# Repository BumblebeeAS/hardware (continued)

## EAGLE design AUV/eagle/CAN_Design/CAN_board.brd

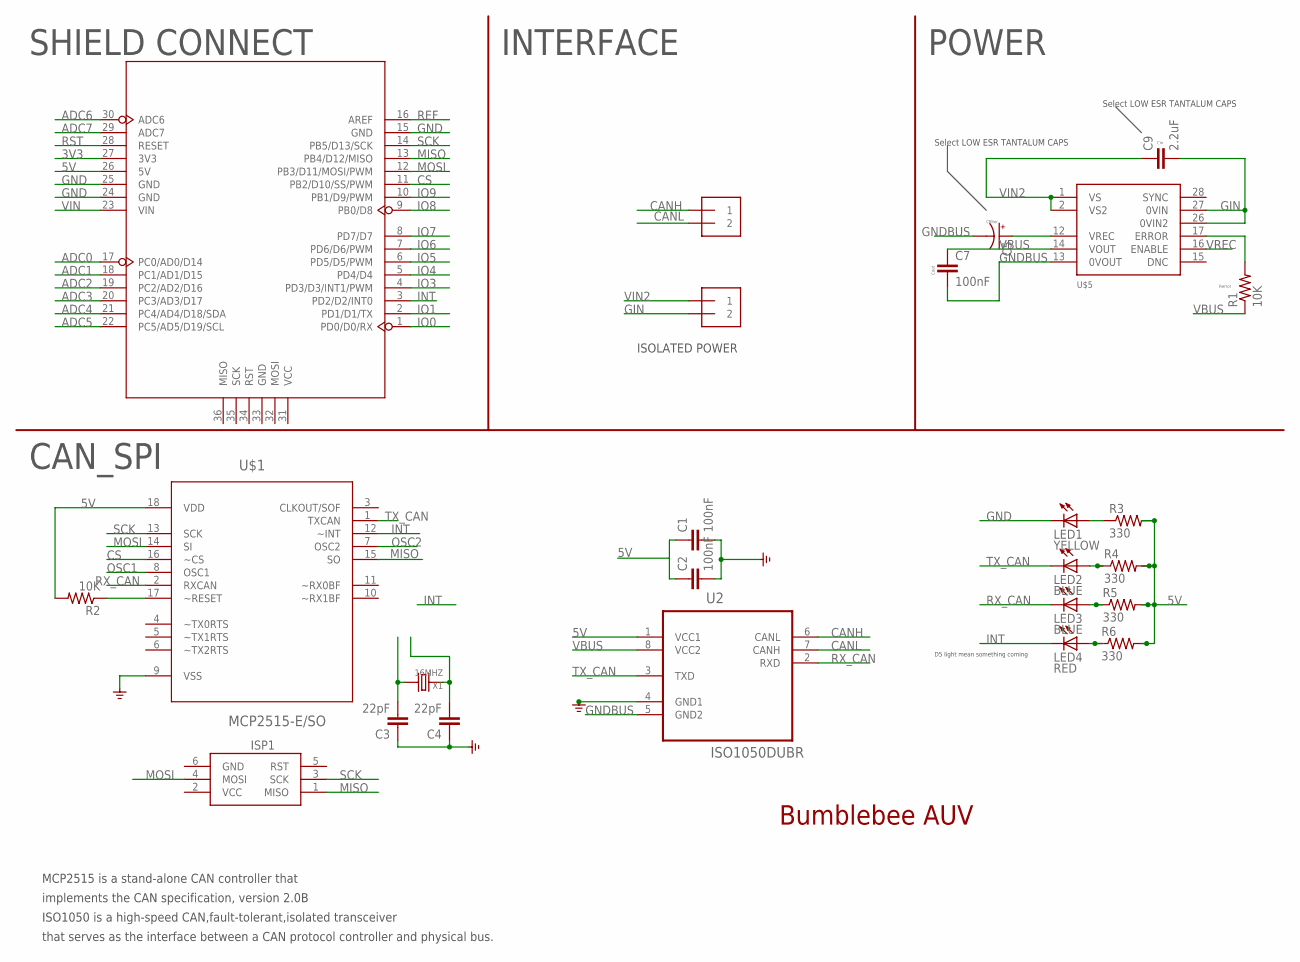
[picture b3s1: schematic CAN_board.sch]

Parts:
C1, C2, C7: 100nF; 0805
C3, C4: 22pF; 0805; MPN MC0603N220K500CT
C5: CAP_POL6032; EIA6032
C9: 2.2uF; 0603-CAP
ISP1: AVRISP-6; AVRISP
J0, J1: 1X2-3.5MM
LED1: YELLOW; CHIPLED_0805
LED2, LED3: BLUE; CHIPLED_0805
LED4: RED; CHIPLED_0805
R1, R2: 10K; 0805
R3, R4, R5, R6: 330; 0805
U2: ISO1050DUBR; SOIC254P1040X485-8N
U3: ARDUINO
U$1: MCP2515-E/SO; SOIC127P1030X265-18N
U$5: DCR01SO; DCR01-SOIC28
X1: 16MHZ; HC49US; MPN HC49US16.000MABJ-UB

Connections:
3V3: U3.27 (3V3)
5V: C1.1, C2.1, R2.2, R3.2, R4.2, R5.2, R6.2, U3.26 (5V), U$1.18 (VDD)
ADC0: U3.17 (PC0/AD0/D14)
ADC1: U3.18 (PC1/AD1/D15)
ADC2: U3.19 (PC2/AD2/D16)
ADC3: U3.20 (PC3/AD3/D17)
ADC4: U3.21 (PC4/AD4/D18/SDA)
ADC5: U3.22 (PC5/AD5/D19/SCL)
ADC6: U3.30 (ADC6)
ADC7: U3.29 (ADC7)
CANH: J0.1
CANL: J0.2
CS: U3.11 (PB2/D10/SS/PWM)
ERROR: R1.2, U$5.17 (ERROR)
GIN: C9.2, J1.2, U$5.26 (0VIN2), U$5.27 (0VIN)
GND: C1.2, C2.2, C3.1, C4.1, ISP1.6 (GND), LED1.C, U3.15 (GND), U3.24 (GND), U3.25 (GND), U$1.9 (VSS)
GNDBUS: C5.P$2 (-), C7.2, U$5.13 (0VOUT)
INT: LED4.C, U3.3 (PD2/D2/INT0), U$1.12 (~INT)
IO0: U3.1 (PD0/D0/RX)
IO1: U3.2 (PD1/D1/TX)
IO3: U3.4 (PD3/D3/INT1/PWM)
IO4: U3.5 (PD4/D4)
IO5: U3.6 (PD5/D5/PWM)
IO6: U3.7 (PD6/D6/PWM)
IO7: U3.8 (PD7/D7)
IO8: U3.9 (PB0/D8)
IO9: U3.10 (PB1/D9/PWM)
MISO: ISP1.1 (MISO), U3.13 (PB4/D12/MISO)
MOSI: ISP1.4 (MOSI), U3.12 (PB3/D11/MOSI/PWM)
unnamed: LED1.A, R3.1
unnamed: LED2.A, R4.1
unnamed: R2.1, U$1.17 (~RESET)
unnamed: LED3.A, R5.1
unnamed: LED4.A, R6.1
OSC1: C3.2, U$1.8 (OSC1), X1.2
OSC2: C4.2, U$1.7 (OSC2), X1.1
REF: U3.16 (AREF)
RST: U3.28 (RESET)
RX_CAN: LED3.C
SCK: ISP1.3 (SCK), U3.14 (PB5/D13/SCK)
TX_CAN: LED2.C
VBUS: C7.1, R1.1, U$5.14 (VOUT)
VCC: ISP1.2 (VCC)
VCC1: U2.1 (VCC1)
VCC2: U2.8 (VCC2)
VIN: U3.23 (VIN)
VIN2: C9.1, J1.1, U$5.1 (VS), U$5.2 (VS2)
VREC: C5.P$1 (+), U$5.12 (VREC), U$5.16 (ENABLE)

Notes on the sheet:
CAN_SPI
SHIELD CONNECT
INTERFACE
POWER
D5 light mean something coming
MCP2515 is a stand-alone CAN controller that
ISO1050 is a high-speed CAN,fault-tolerant,isolated transceiver
that serves as the interface between a CAN protocol controller and physical bus.
implements the CAN specification, version 2.0B
Bumblebee AUV
ISOLATED POWER
Cfilter
Cout
Cin
Rerror
Select LOW ESR TANTALUM CAPS

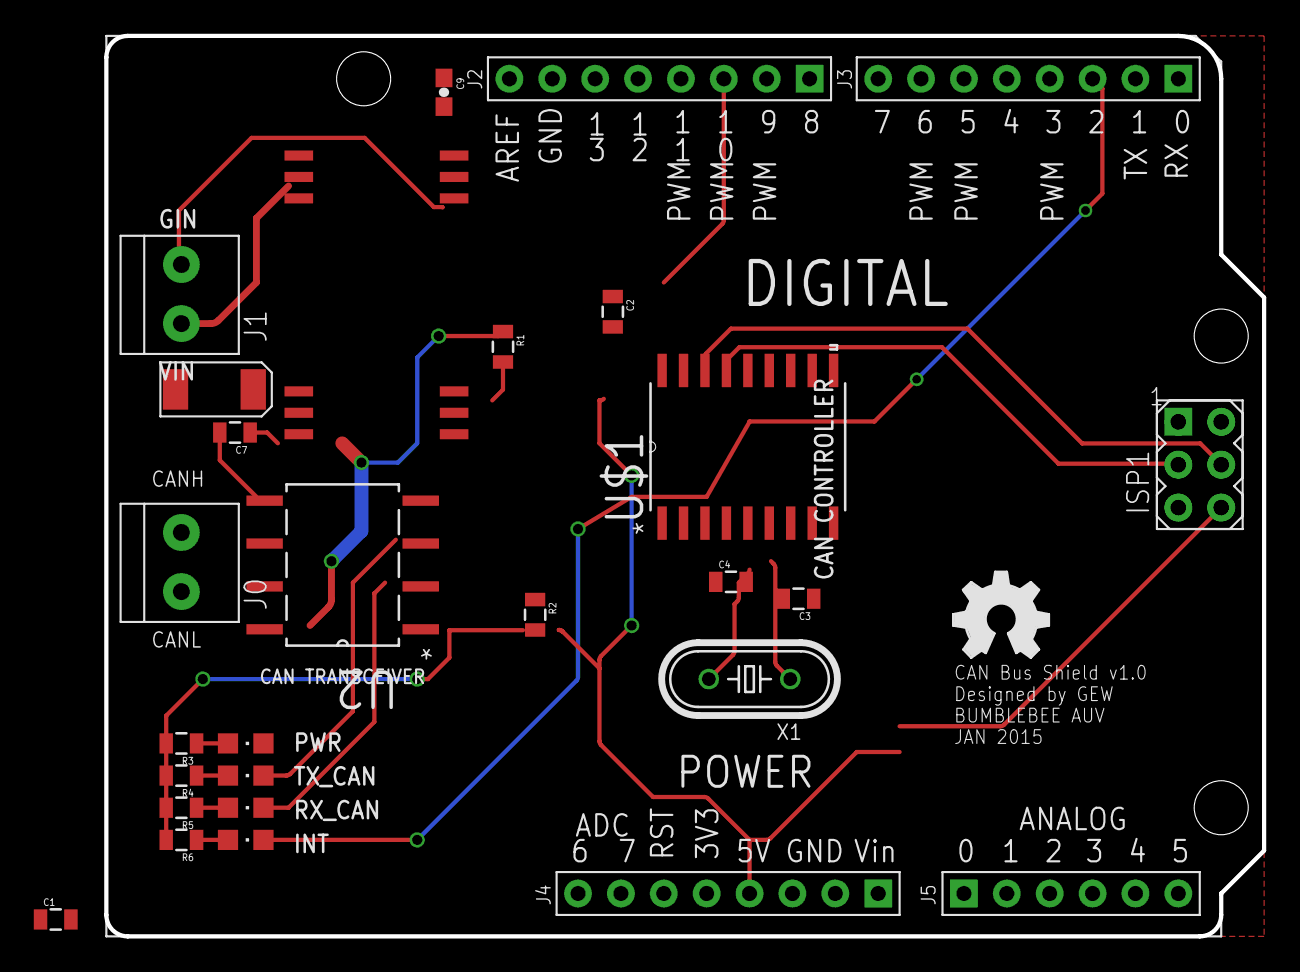
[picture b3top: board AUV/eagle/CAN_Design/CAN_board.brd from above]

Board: 4 copper layers, 68.6 x 53.3 mm, 26 parts (0 on the bottom side), 19 nets.

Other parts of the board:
U$2: OSHW_FILLX200_NOTEXT

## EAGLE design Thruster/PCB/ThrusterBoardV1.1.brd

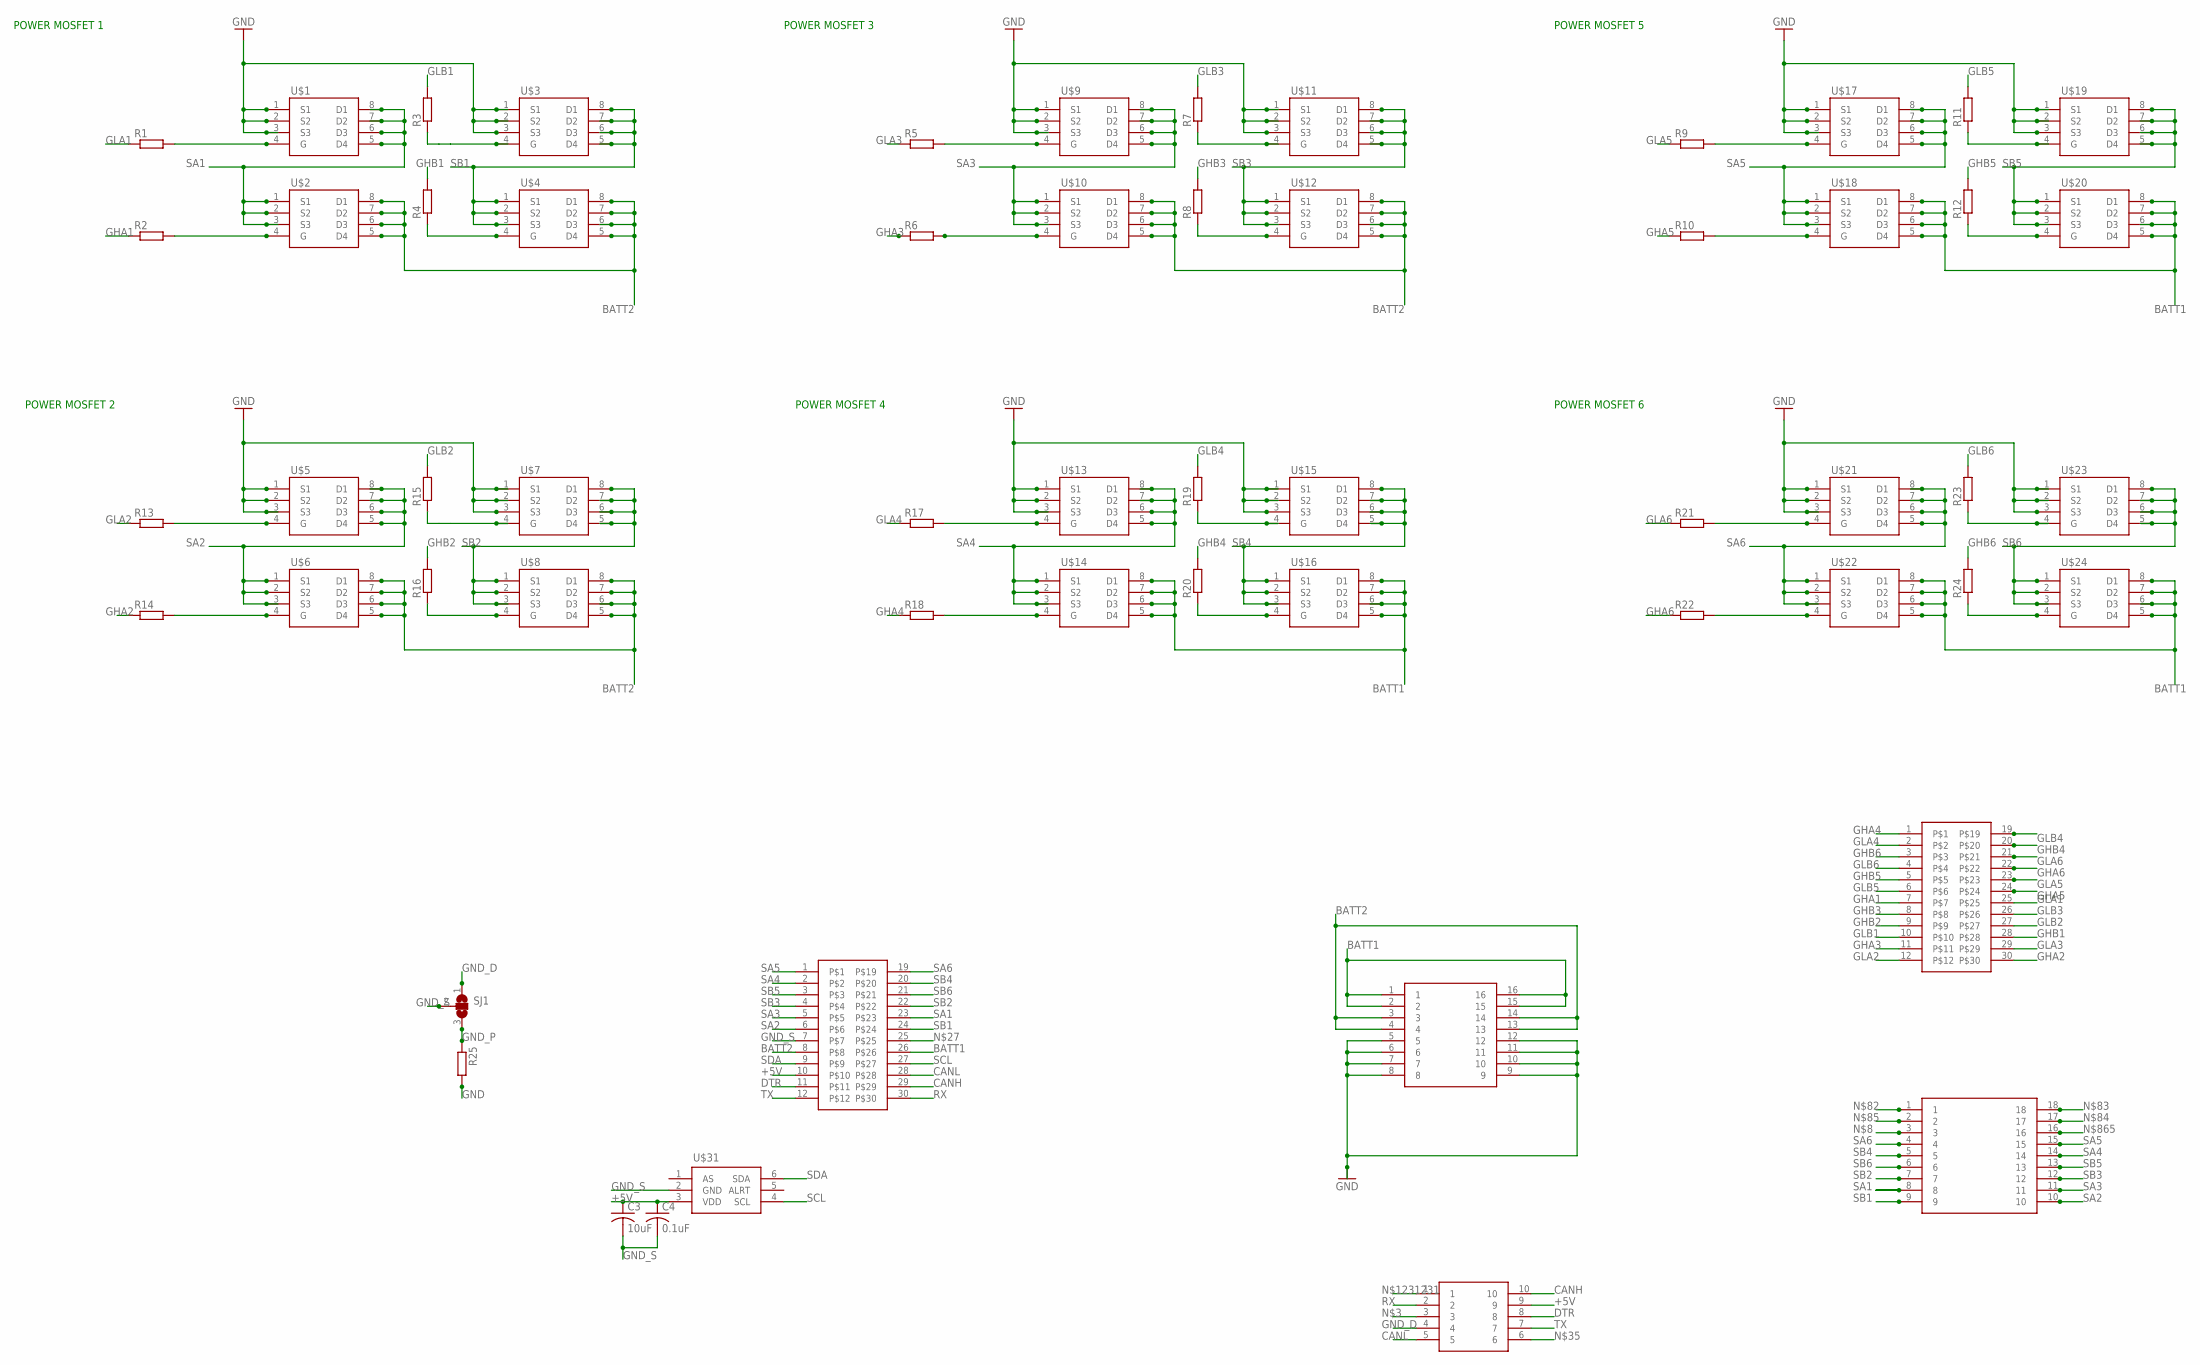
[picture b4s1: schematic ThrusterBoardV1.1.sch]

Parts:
C3: 10uF; C0805
C4: 0.1uF; C0805
R1, R2, R3, R4, R5, R6, R7, R8, R9, R10, R11, R12, R13, R14, R15, R16, R17, R18, R19, R20, R21, R22, R23, R24, R25: R; R0805
SJ1: SJ2W; SJ_2
U$1, U$2, U$3, U$4, U$5, U$6, U$7, U$8, U$9, U$10, U$11, U$12, U$13, U$14, U$15, U$16, U$17, U$18, U$19, U$20, U$21, U$22, U$23, U$24: IRF7842PBF; SO-8
U$25: 15-24-6163
U$26: 50-36-1836
U$27: 15-24-6103
U$28, U$29: 15-45-3136
U$31: AD7414; SOT23-6

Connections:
+5V: C3.1, C4.1, U$27.9, U$29.10, U$31.3 (VDD)
ASDASD: R2.2, U$2.4 (G)
BATT1: U$14.5 (D4), U$14.6 (D3), U$14.7 (D2), U$14.8 (D1), U$16.5 (D4), U$16.6 (D3), U$16.7 (D2), U$16.8 (D1), U$18.5 (D4), U$18.6 (D3), U$18.7 (D2), U$18.8 (D1), U$20.5 (D4), U$20.6 (D3), U$20.7 (D2), U$20.8 (D1), U$22.5 (D4), U$22.6 (D3), U$22.7 (D2), U$22.8 (D1), U$24.5 (D4), U$24.6 (D3), U$24.7 (D2), U$24.8 (D1), U$25.1, U$25.2, U$25.15, U$25.16, U$29.26
BATT2: U$2.5 (D4), U$2.6 (D3), U$2.7 (D2), U$2.8 (D1), U$4.5 (D4), U$4.6 (D3), U$4.7 (D2), U$4.8 (D1), U$6.5 (D4), U$6.6 (D3), U$6.7 (D2), U$6.8 (D1), U$8.5 (D4), U$8.6 (D3), U$8.7 (D2), U$8.8 (D1), U$10.5 (D4), U$10.6 (D3), U$10.7 (D2), U$10.8 (D1), U$12.5 (D4), U$12.6 (D3), U$12.7 (D2), U$12.8 (D1), U$25.3, U$25.4, U$25.13, U$25.14, U$29.8
CANH: U$27.10, U$29.29
CANL: U$27.5, U$29.28
DTR: U$27.8, U$29.11
GHA1: R2.1, U$28.7
GHA2: R14.1, U$28.30
GHA3: R6.1, U$28.11
GHA4: R18.1, U$28.1
GHA5: R10.1, U$28.24
GHA6: R22.1, U$28.22
GHB1: R4.2, U$28.28
GHB2: R16.2, U$28.9
GHB3: R8.2, U$28.8
GHB4: R20.2, U$28.20
GHB5: R12.2, U$28.5
GHB6: R24.2, U$28.3
GLA1: R1.1, U$28.25
GLA2: R13.1, U$28.12
GLA3: R5.1, U$28.29
GLA4: R17.1, U$28.2
GLA5: R9.1, U$28.23
GLA6: R21.1, U$28.21
GLB1: R3.2, U$28.10
GLB2: R15.2, U$28.27
GLB3: R7.2, U$28.26
GLB4: R19.2, U$28.19
GLB5: R11.2, U$28.6
GLB6: R23.2, U$28.4
GND: R25.2, U$1.1 (S1), U$1.2 (S2), U$1.3 (S3), U$3.1 (S1), U$3.2 (S2), U$3.3 (S3), U$5.1 (S1), U$5.2 (S2), U$5.3 (S3), U$7.1 (S1), U$7.2 (S2), U$7.3 (S3), U$9.1 (S1), U$9.2 (S2), U$9.3 (S3), U$11.1 (S1), U$11.2 (S2), U$11.3 (S3), U$13.1 (S1), U$13.2 (S2), U$13.3 (S3), U$15.1 (S1), U$15.2 (S2), U$15.3 (S3), U$17.1 (S1), U$17.2 (S2), U$17.3 (S3), U$19.1 (S1), U$19.2 (S2), U$19.3 (S3), U$21.1 (S1), U$21.2 (S2), U$21.3 (S3), U$23.1 (S1), U$23.2 (S2), U$23.3 (S3), U$25.5, U$25.6, U$25.7, U$25.8, U$25.9, U$25.10, U$25.11, U$25.12
GND_D: SJ1.1, U$27.4
GND_P: R25.1, SJ1.3
GND_S: C3.2, C4.2, SJ1.2, U$29.7, U$31.2 (GND)
unnamed: R3.1, U$3.4 (G)
unnamed: R4.1, U$4.4 (G)
unnamed: R5.2, U$9.4 (G)
unnamed: R6.2, U$10.4 (G)
unnamed: R7.1, U$11.4 (G)
unnamed: R8.1, U$12.4 (G)
unnamed: R9.2, U$17.4 (G)
unnamed: R10.2, U$18.4 (G)
unnamed: R11.1, U$19.4 (G)
unnamed: R12.1, U$20.4 (G)
unnamed: R13.2, U$5.4 (G)
unnamed: R14.2, U$6.4 (G)
unnamed: R16.1, U$8.4 (G)
unnamed: R15.1, U$7.4 (G)
unnamed: R17.2, U$13.4 (G)
unnamed: R18.2, U$14.4 (G)
unnamed: R20.1, U$16.4 (G)
unnamed: R19.1, U$15.4 (G)
unnamed: R21.2, U$21.4 (G)
unnamed: R22.2, U$22.4 (G)
unnamed: R23.1, U$23.4 (G)
unnamed: R24.1, U$24.4 (G)
unnamed: R1.2, U$1.4 (G)
RX: U$27.2, U$29.30
SA1: U$1.5 (D4), U$1.6 (D3), U$1.7 (D2), U$1.8 (D1), U$2.1 (S1), U$2.2 (S2), U$2.3 (S3), U$26.8, U$29.23
SA2: U$5.5 (D4), U$5.6 (D3), U$5.7 (D2), U$5.8 (D1), U$6.1 (S1), U$6.2 (S2), U$6.3 (S3), U$26.10, U$29.6
SA3: U$9.5 (D4), U$9.6 (D3), U$9.7 (D2), U$9.8 (D1), U$10.1 (S1), U$10.2 (S2), U$10.3 (S3), U$26.11, U$29.5
SA4: U$13.5 (D4), U$13.6 (D3), U$13.7 (D2), U$13.8 (D1), U$14.1 (S1), U$14.2 (S2), U$14.3 (S3), U$26.14, U$29.2
SA5: U$17.5 (D4), U$17.6 (D3), U$17.7 (D2), U$17.8 (D1), U$18.1 (S1), U$18.2 (S2), U$18.3 (S3), U$26.15, U$29.1
SA6: U$21.5 (D4), U$21.6 (D3), U$21.7 (D2), U$21.8 (D1), U$22.1 (S1), U$22.2 (S2), U$22.3 (S3), U$26.4, U$29.19
SB1: U$3.5 (D4), U$3.6 (D3), U$3.7 (D2), U$3.8 (D1), U$4.1 (S1), U$4.2 (S2), U$4.3 (S3), U$26.9, U$29.24
SB2: U$7.5 (D4), U$7.6 (D3), U$7.7 (D2), U$7.8 (D1), U$8.1 (S1), U$8.2 (S2), U$8.3 (S3), U$26.7, U$29.22
SB3: U$11.5 (D4), U$11.6 (D3), U$11.7 (D2), U$11.8 (D1), U$12.1 (S1), U$12.2 (S2), U$12.3 (S3), U$26.12, U$29.4
SB4: U$15.5 (D4), U$15.6 (D3), U$15.7 (D2), U$15.8 (D1), U$16.1 (S1), U$16.2 (S2), U$16.3 (S3), U$26.5, U$29.20
SB5: U$19.5 (D4), U$19.6 (D3), U$19.7 (D2), U$19.8 (D1), U$20.1 (S1), U$20.2 (S2), U$20.3 (S3), U$26.13, U$29.3
SB6: U$23.5 (D4), U$23.6 (D3), U$23.7 (D2), U$23.8 (D1), U$24.1 (S1), U$24.2 (S2), U$24.3 (S3), U$26.6, U$29.21
SCL: U$29.27, U$31.4 (SCL)
SDA: U$29.9, U$31.6 (SDA)
TX: U$27.7, U$29.12

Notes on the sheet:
POWER MOSFET 1
POWER MOSFET 2
POWER MOSFET 3
POWER MOSFET 4
POWER MOSFET 5
POWER MOSFET 6

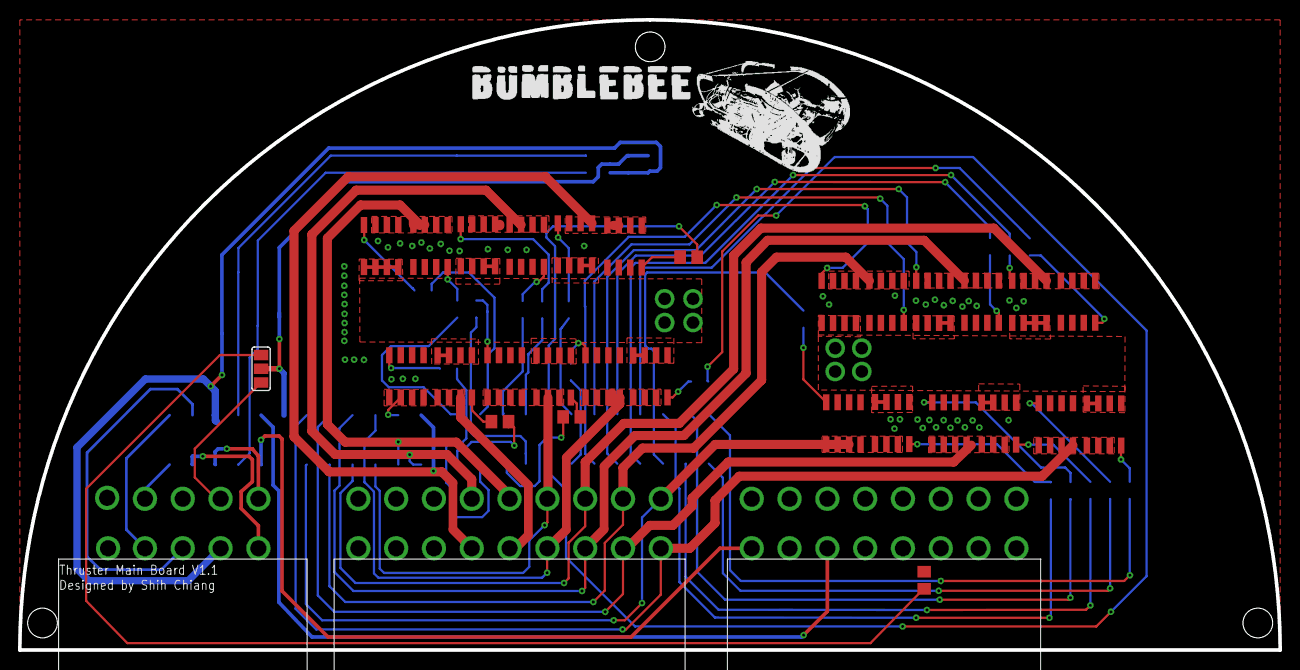
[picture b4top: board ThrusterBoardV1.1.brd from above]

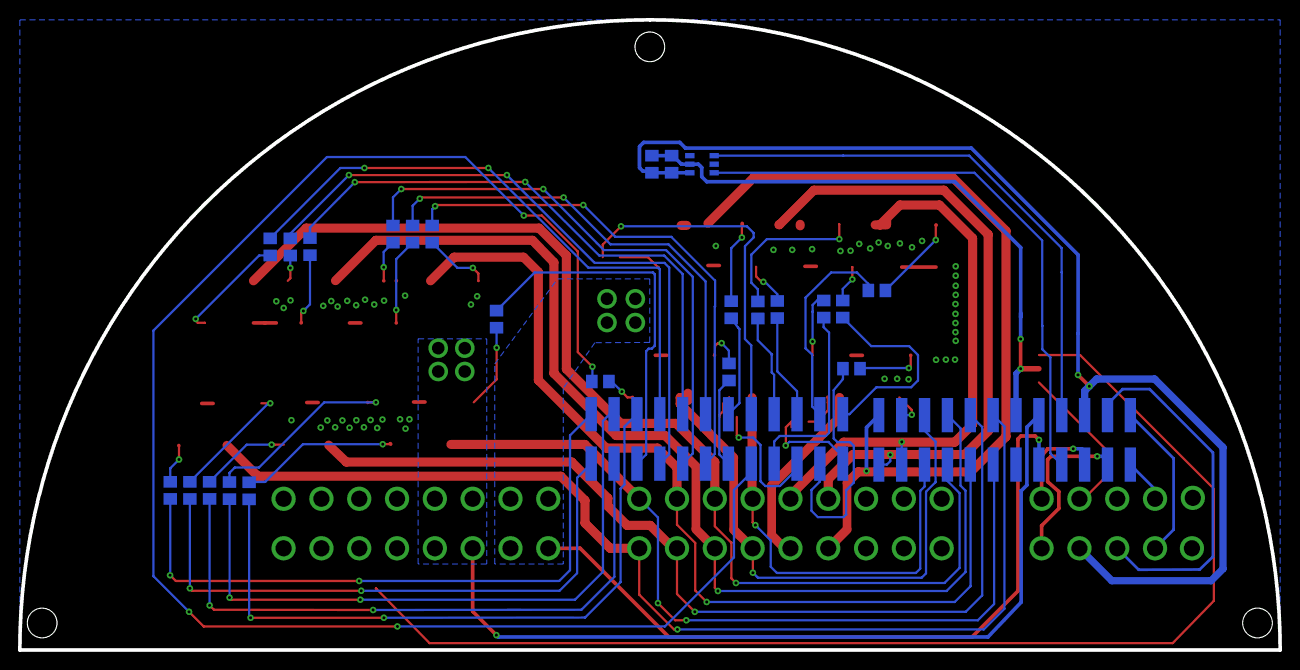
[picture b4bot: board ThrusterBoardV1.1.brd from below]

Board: 2 copper layers, 140.0 x 70.0 mm, 58 parts (26 on the bottom side), 74 nets.

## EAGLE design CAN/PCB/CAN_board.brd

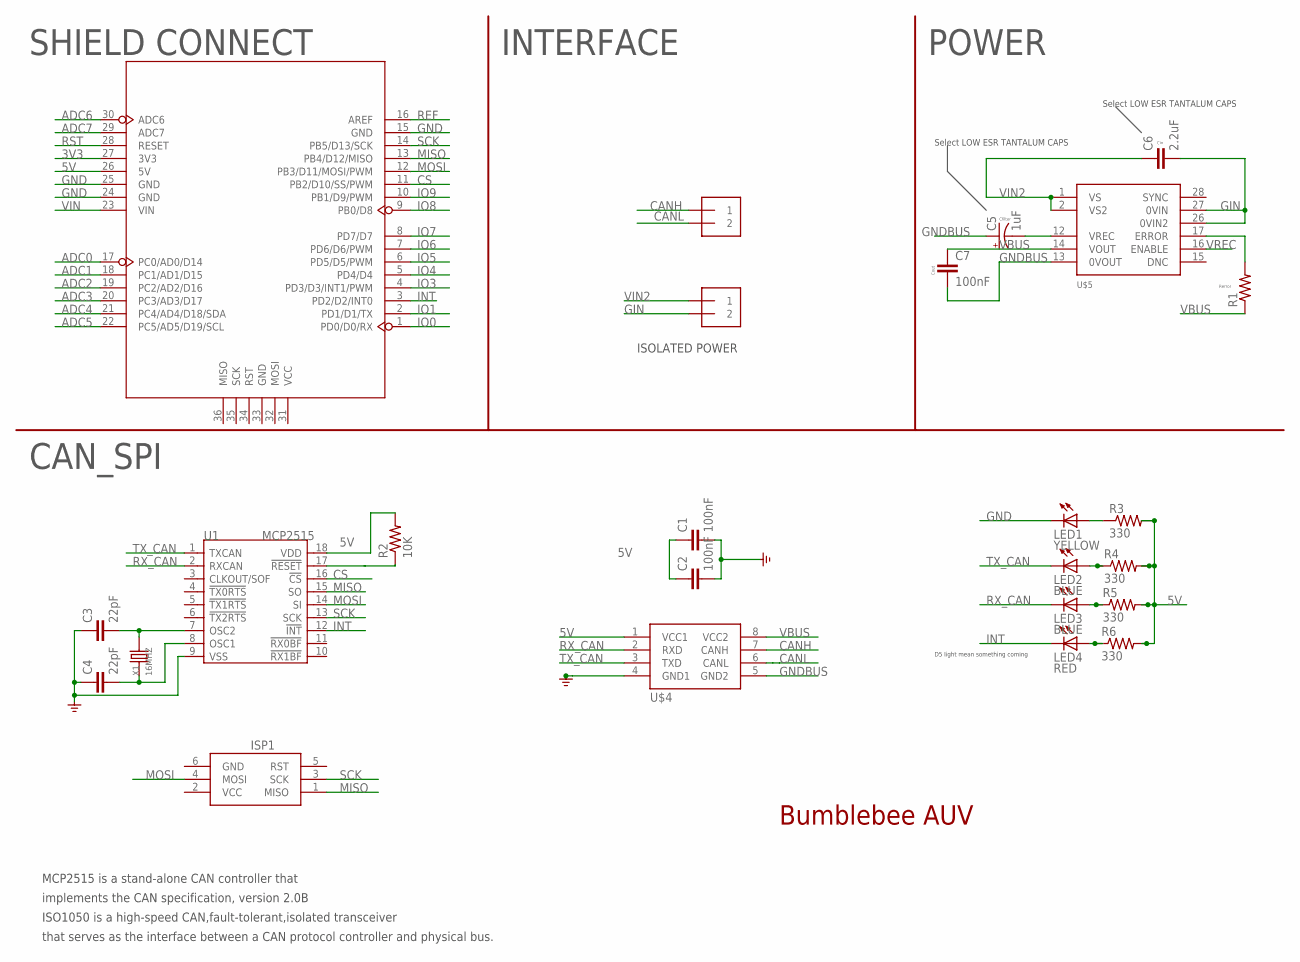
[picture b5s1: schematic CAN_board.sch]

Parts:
C1, C2, C7: 100nF; 0805; MPN MC0805B104K250CT
C3, C4: 22pF; 0805; MPN MC0603N220K500CT
C5: 1uF; EIA6032; MPN TR3C105K050C1600
C6: 2.2uF; 0603-CAP; MPN F381A225MMA
ISP1: AVRISP-6; AVRISP
J0, J1: 1X2-3.5MM
LED1: YELLOW; CHIPLED_0805; MPN KPT-2012SYCK-J3
LED2, LED3: BLUE; CHIPLED_0805; MPN 150080BS75000
LED4: RED; CHIPLED_0805; MPN KPT-2012SRC-J4
R1: RESISTOR0805-RES; 0805
R2: 10K; 0805; MPN CRCW080510K0FKTA
R3, R4, R5, R6: 330; 0805; MPN MCHP05W4F3300T5E
U1: MCP2515; SOIC18; MPN MCP2515-I/SO
U3: ARDUINO
U$4: ISO1050; DUB-8; MPN ISO1050DUBR
U$5: DCR01SO; DCR01-SOIC28; MPN DCR010505U
X1: 16MHZ; HC49US; MPN HC-49/U-S16000000ABJB

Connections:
3V3: U3.27 (3V3)
5V: C1.1, C2.1, R2.2, R3.2, R4.2, R5.2, R6.2, U1.18 (VDD), U3.26 (5V), U$4.1 (VCC1)
ADC0: U3.17 (PC0/AD0/D14)
ADC1: U3.18 (PC1/AD1/D15)
ADC2: U3.19 (PC2/AD2/D16)
ADC3: U3.20 (PC3/AD3/D17)
ADC4: U3.21 (PC4/AD4/D18/SDA)
ADC5: U3.22 (PC5/AD5/D19/SCL)
ADC6: U3.30 (ADC6)
ADC7: U3.29 (ADC7)
CANH: J0.1, U$4.7 (CANH)
CANL: J0.2, U$4.6 (CANL)
CS: U1.16 (!CS), U3.11 (PB2/D10/SS/PWM)
ERROR: R1.2, U$5.17 (ERROR)
GIN: C6.2, J1.2, U$5.26 (0VIN2), U$5.27 (0VIN)
GND: C1.2, C2.2, C3.1, C4.1, ISP1.6 (GND), LED1.C, U1.9 (VSS), U3.15 (GND), U3.24 (GND), U3.25 (GND), U$4.4 (GND1)
GNDBUS: C5.P$1 (+), C7.2, U$4.5 (GND2), U$5.13 (0VOUT)
INT: LED4.C, U1.12 (!INT), U3.3 (PD2/D2/INT0)
IO0: U3.1 (PD0/D0/RX)
IO1: U3.2 (PD1/D1/TX)
IO3: U3.4 (PD3/D3/INT1/PWM)
IO4: U3.5 (PD4/D4)
IO5: U3.6 (PD5/D5/PWM)
IO6: U3.7 (PD6/D6/PWM)
IO7: U3.8 (PD7/D7)
IO8: U3.9 (PB0/D8)
IO9: U3.10 (PB1/D9/PWM)
MISO: ISP1.1 (MISO), U1.15 (SO), U3.13 (PB4/D12/MISO)
MOSI: ISP1.4 (MOSI), U1.14 (SI), U3.12 (PB3/D11/MOSI/PWM)
unnamed: LED1.A, R3.1
unnamed: LED2.A, R4.1
unnamed: LED3.A, R5.1
unnamed: C3.2, U1.7 (OSC2), X1.2
unnamed: C4.2, U1.8 (OSC1), X1.1
unnamed: LED4.A, R6.1
REF: U3.16 (AREF)
RST: U3.28 (RESET)
RST_N: R2.1, U1.17 (!RESET)
RX_CAN: LED3.C, U1.2 (RXCAN), U$4.2 (RXD)
SCK: ISP1.3 (SCK), U1.13 (SCK), U3.14 (PB5/D13/SCK)
TX_CAN: LED2.C, U1.1 (TXCAN), U$4.3 (TXD)
VBUS: C7.1, R1.1, U$4.8 (VCC2), U$5.14 (VOUT)
VCC: ISP1.2 (VCC)
VIN: U3.23 (VIN)
VIN2: C6.1, J1.1, U$5.1 (VS), U$5.2 (VS2)
VREC: C5.P$2 (-), U$5.12 (VREC), U$5.16 (ENABLE)

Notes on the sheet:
CAN_SPI
SHIELD CONNECT
INTERFACE
POWER
D5 light mean something coming
MCP2515 is a stand-alone CAN controller that
ISO1050 is a high-speed CAN,fault-tolerant,isolated transceiver
that serves as the interface between a CAN protocol controller and physical bus.
implements the CAN specification, version 2.0B
Bumblebee AUV
ISOLATED POWER
Cfilter
Cout
Cin
Rerror
Select LOW ESR TANTALUM CAPS

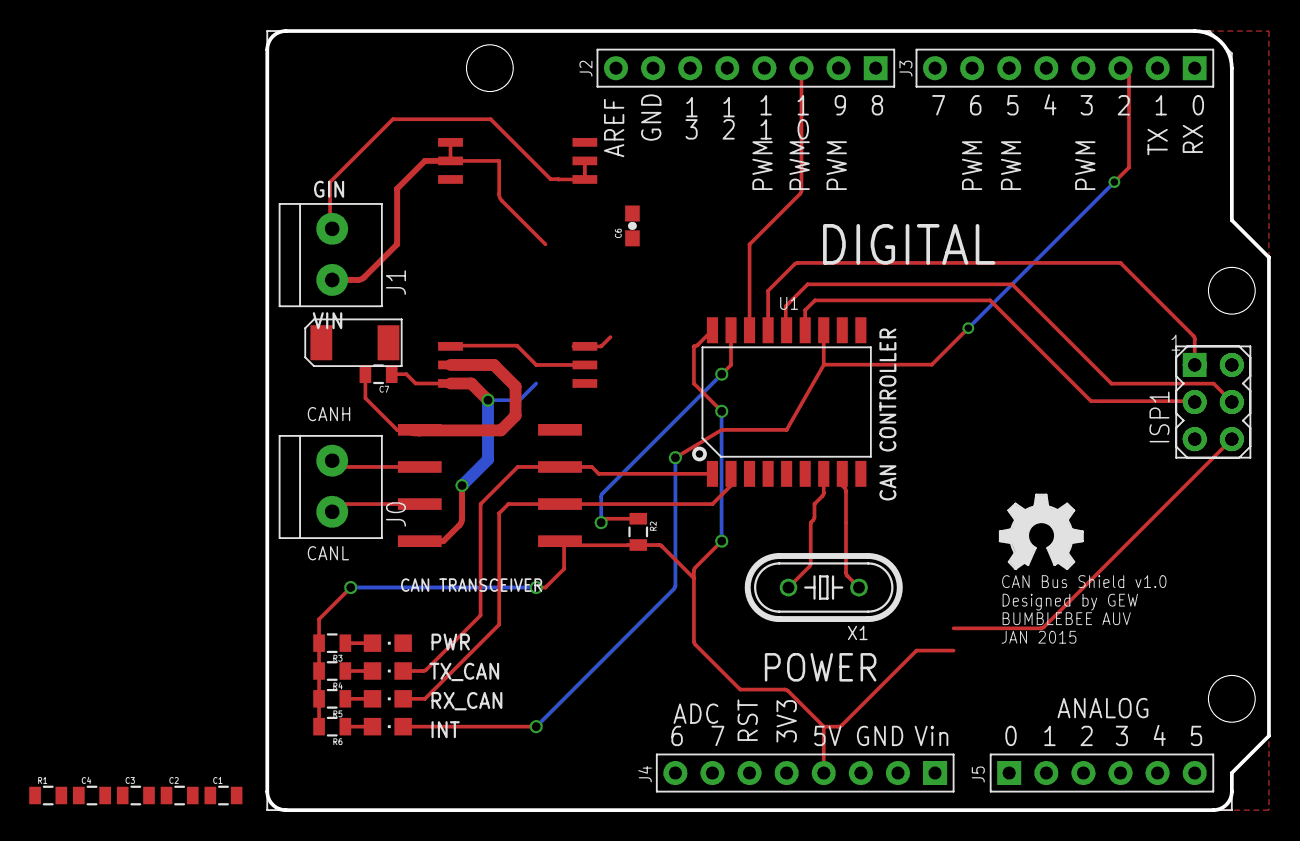
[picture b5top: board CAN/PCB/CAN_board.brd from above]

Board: 4 copper layers, 68.6 x 53.3 mm, 26 parts (0 on the bottom side), 24 nets.

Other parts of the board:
U$2: OSHW_FILLX200_NOTEXT

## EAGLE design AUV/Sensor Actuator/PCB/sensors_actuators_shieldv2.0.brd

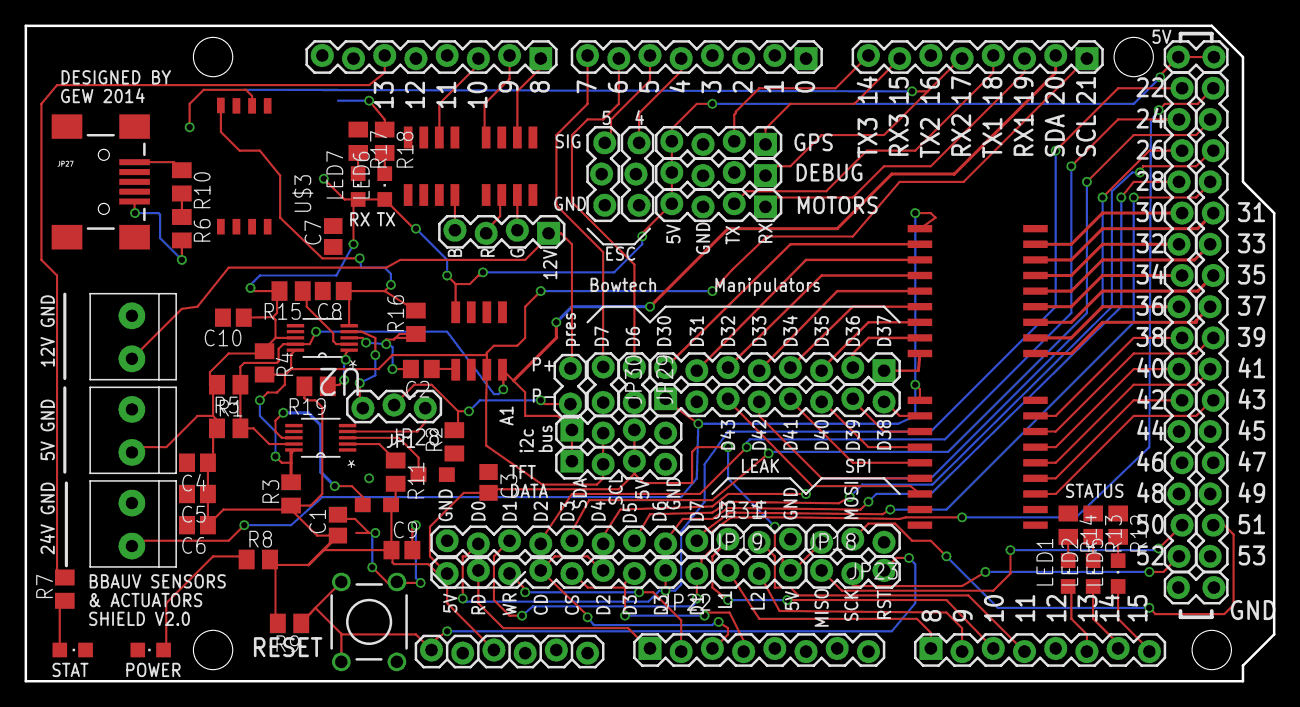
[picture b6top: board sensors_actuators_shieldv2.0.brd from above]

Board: 4 copper layers, 101.6 x 53.3 mm, 82 parts (1 on the bottom side), 98 nets.

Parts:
B1, B2: MMZ2012Y152B0.4OHM,500MA; 0805
C1, C7, C10: 1uF; C0805
C2: 0.1uF; C0805
C3: 0.22uF; C0805
C4, C5, C9: 100nF; C0805
C6: 4.7uF; C0805
C8: 47pF; C0805
D1, D2: ULN2803ADW; SOIC
J1, J2, J3: 1X2-3.5MM
JP1, JP2, JP3, JP5, JP6, JP16, JP17: 1X08_LOCK
JP4, JP14, JP24, JP29, JP30: 1X02_LOCK
JP7, JP8, JP9, JP20, JP21, JP26: 1X04_LOCK
JP10, JP11, JP18, JP19, JP23, JP28, JP31: 1X03_LOCK
JP12, JP13: M16LOCK; 1X16_LOCK
JP15: 1X06_LOCK
JP22, JP25: M09LOCK; 1X09_LOCK
JP27: USBSMD; USB-MINIB
LED1, LED4: BLUE; CHIPLED_0805
LED2, LED3: YELLOW; CHIPLED_0805
LED5: RED; CHIPLED_0805
LED6, LED7: GREEN; CHIPLED_0805
M1, M2: IRF7910PBF; SO-8
R1, R3, R4, R5, R11: 1K; M0805
R2: 250; M0805
R6, R9: 10k; M0805
R7, R8, R12, R13, R14: 330; M0805
R10: 4k7; M0805
R15, R19: 10K; M0805
R16: 51K; M0805
R17, R18: 270; M0805
S1: TACTILE-PTH
U1, U2: ADS1115IDGST; SOP50P490X110-10N
U$1: FT232RL; SSOP-28
U$2: HIH6130; SO-8
U$3: MPXH6250A; SSOP-8

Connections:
5V: B2.1, C1.1, C3.2, C4.1, C5.1, C6.1, C9.1, C10.1, J3.2, JP4.1, JP4.2, JP7.4, JP8.4, JP9.4, JP15.3, JP19.3, JP20.3, JP21.3, JP22.9, JP23.3, LED6.A, LED7.A, R1.1, R3.1, R4.1, R5.2, R8.2, R9.2, R11.2, R15.2, R19.2, U2.8, U$1.4, U$1.20, U$2.8, U$3.2
12V: J1.2, JP24.2, JP26.1
24V: D1.10, D2.10, J2.2, JP6.1
A0: JP16.1, JP22.8
A1: JP16.2, JP22.7
A2: JP16.3, JP22.4, JP22.6
A3: JP16.4, JP22.3, JP22.5
A8: JP17.1, JP19.1
A9: JP17.2, JP19.2
A10: JP17.3, JP31.1
A11: JP17.4, JP31.2
A13: JP17.6, LED1.A
A14: JP17.7, LED2.A
A15: JP17.8, LED5.A
D4: JP2.5, JP11.1
D5: JP2.6, JP10.1
D6: JP2.7, JP29.1
D7: JP2.8, JP30.1
D8: JP1.1, M1.2
D9: JP1.2, M1.4
D10: JP1.3, M2.2
D13: JP1.6, R7.2
D22: JP12.1, JP22.2, JP25.2
D23: JP13.16, JP22.1, JP25.3
D24: JP12.2, JP25.4
D25: JP13.15, JP25.5
D26: JP12.3, JP25.6
D27: JP13.14, JP25.7
D28: JP12.4, JP25.8
D29: JP13.13, JP25.9
D30: D2.8, JP12.5
D31: D2.7, JP13.12
D32: D2.6, JP12.6
D33: D2.5, JP13.11
D34: D2.4, JP12.7
D35: D2.3, JP13.10
D36: D2.2, JP12.8
D37: D2.1, JP13.9
D38: D1.8, JP12.9
D39: D1.7, JP13.8
D40: D1.6, JP12.10
D41: D1.5, JP13.7
D42: D1.4, JP12.11
D43: D1.3, JP13.6
D50: JP12.15, JP18.1
D51: JP13.2, JP23.2
D52: JP12.16, JP18.2
GND: B1.2, C1.2, C2.2, C3.1, C4.2, C5.2, C6.2, C7.1, C8.2, C9.2, C10.2, D1.9, D2.9, J1.1, J2.1, J3.1, JP1.7, JP7.3, JP8.3, JP9.3, JP10.3, JP11.3, JP14.1, JP14.2, JP15.4, JP15.5, JP20.4, JP21.4, JP23.1, JP25.1, JP27.GND, JP29.2, JP30.2, JP31.3, LED3.C, LED4.C, M1.1, M1.3, M2.1, R2.1, R6.2, R12.1, R13.1, R14.1, R16.1, S1.1, S1.2, U1.1, U2.3, U$1.7, U$1.18, U$1.21, U$1.25, U$1.26, U$2.2, U$3.3
unnamed: R6.1, R10.2, U$1.19
unnamed: LED7.C, R17.2
unnamed: D1.16, JP6.3
unnamed: D1.15, JP6.4
unnamed: JP28.1, U1.4
unnamed: B1.1, U1.3
unnamed: D1.14, JP6.5
unnamed: D1.13, JP6.6
unnamed: D1.12, JP6.7
unnamed: D1.11, JP6.8
unnamed: D2.18, JP5.1
unnamed: D2.17, JP5.2
unnamed: D2.14, JP5.5
unnamed: D2.15, JP5.4
unnamed: D2.11, JP5.8
unnamed: D2.13, JP5.6
unnamed: D2.12, JP5.7
unnamed: JP26.2, M1.7
unnamed: D2.16, JP5.3
unnamed: JP26.3, M1.6
unnamed: JP26.4, M2.8
unnamed: R11.1, U1.2
unnamed: C2.1, U$2.1
unnamed: B2.2, U1.8
unnamed: LED1.C, R14.2
unnamed: JP27.VBUS, R10.1
unnamed: C7.2, U$1.17
unnamed: LED2.C, R13.2
unnamed: LED5.C, R12.2
unnamed: R15.1, U2.2
unnamed: LED6.C, R18.2
unnamed: R19.1, U2.1
unnamed: LED3.A, R8.1
unnamed: LED4.A, R7.1
PRES_SENSE: C8.1, R16.2, U2.5, U$3.4
RES: JP15.1, JP18.3, R9.1, S1.3, S1.4
RX1: JP3.3, JP9.1
RX2: JP3.5, JP8.1, U$1.1
RX3: JP3.7, JP7.1
RXLED: R17.1, U$1.22
SCL: JP3.1, JP20.2, JP21.2, R3.2, R4.2, U1.10, U2.10, U$2.3
SDA: JP3.2, JP20.1, JP21.1, R1.2, R5.1, U1.9, U2.9, U$2.4
SENSE: JP24.1, JP28.2, R2.2
SENSE2: JP28.3, U2.4
TX1: JP3.4, JP9.2
TX2: JP3.6, JP8.2, U$1.5
TX3: JP3.8, JP7.2
TXLED: R18.1, U$1.23
USBDM: JP27.D-, U$1.16
USBDP: JP27.D+, U$1.15
